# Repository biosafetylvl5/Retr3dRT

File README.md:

# Retr3dRT
RAMPS 1.4 self-test board designed for used in conjunction with Retr3d.

## Images

#### OSHPark Renderings

# Make Retr3dRT

## Parts

Check your parts! The easiest way to make an functional Retr3dRT and not know why it's not working to use the wrong parts.

Part            | Picture                                                                                                   | Description                                                | Quantity |                                                                              Distributer
--------------- | --------------------------------------------------------------------------------------------------------- | ---------------------------------------------------------- | :------: | ---------------------------------------------------------------------------------------:
Retr3dRT        |              | Circuit board, see "PCB Fabrication" for more info         |    1     |                                                                    OSH Park, SeeedStudio
4610X-101-502LF |  | Nine 5K Ohm Resistor Array, 10SIP                          |    2     |                                           [DigiKey](http://www.digikey.com/short/3p0zrv)
4610X-101-153LF |  | Five 15k Ohm Resistor Array, 10SIP                         |    4     |                                           [DigiKey](http://www.digikey.com/short/3p0zw4)
LED-3MM         |             | 3mm LED (Preferably Green)                                 |    1     |                                    [DigiKey](http://www.digikey.com/short/3p0z0f), Other
R1, R2          |         | 5k Ohm Resistor                                            |    2     |                                    [DigiKey](http://www.digikey.com/short/3p0z1c), Other
R3              |        | LED Current Limiting Resistor (520 Ohm is a safe estimate) |    1     |                                    [DigiKey](http://www.digikey.com/short/3p0z1r), Other
3461260P1       |       | DIP Long Blue Female Header                                |    7     | [Pending](http://www.seeedstudio.com/wiki/File:1X6P-2.54-8.5%2B2.5-12.3-BLUE-FEMALE.zip)

## Soldering

Now that you have your parts, let's get assembling! If you are just getting started in Electronics, check out [Lady Ada's Guide to Excellent Soldering](https://learn.adafruit.com/adafruit-guide-excellent-soldering/) to brush up on your soldering skills.

Start by soldering R1, R2, and R3 into place. Follow by soldering the LED paying special attention to the polarity annotated on the board. Next, solder the 4610X-101-153LFs and 4610X-101-502LFs by placing them in their holes and securing them with sticky tape. The stick tape prevents them from falling out as you turn the board upside down to solder.

Now, you should have all of the components except for the header soldered. To start the headers, get your diagonal cutters out. Use the diagonal cutters to cut the twelve long headers into eight four long headers, two five long header, one six long header, one eight long header and one complete twelve long header. Now that all of your headers have been prepared, plug them into your RAMPS control board that has its **stepper drivers installed**. Now, carefully lower your Retr3dRT onto the pins and solder it in place.

## Using

Download [Retr3dRT.ino](https://raw.githubusercontent.com/biosafetylvl5/Retr3dRT/master/Retr3dRT.ino) from the [Retr3dRT repository](https://github.com/biosafetylvl5/Retr3dRT) and upload it to your Arduino MEGA with both RAMPS and Retr3dRT installed on top. To view the diagnosis, open your serial terminal and bask in the glow of the information.

## Keeping in touch

To keep in touch to watch for updates and improvements you have a few options:

- [Star the Retr3dRT repository](https://github.com/biosafetylvl5/Retr3dRT/stargazers) to be kept up to date
- Follow the [#Retr3dRT hashtag](https://twitter.com/hashtag/Retr3dRT?f=tweets&src=hash) on twitter to know the moment things happen
- Check out [techfortrade](techfortrade.org) to see what else we're doing

## PCB Fabrication
We're lucky enough to live in the era of cheap and abundant PCB fabrication options. However, this abundance of choices does make choosing a formidable task. However, too make the choosing easier for you, we've narrowed down
the choices to two for you. You're free to choose any fabrication vendor, but we will only be offering (unless asked for others) gerber files (PCB blueprints) for SeeedStudio and OSHPark.

### OSHPark
OSHPark is fantastic. Their boards look great and arrive quickly. However, at 5$ per square inch for three boards, they can be costly for larger runs. Other than that, they have produced good results. This is probably the choice for you if you need
three boards or less.

### SeeedStudio
While SeeedStudio is the budget choice, this isn't a statement about their quality. They feature vanilla PCBs that are very functional, but aren't the most aesthetically pleasing. They deliver quickly, but slower than OSHPark (in the USA) given that they're based in china. This is probably the choice for you if you need more than three boards.

### Final Notes

This board assumes that PCB traces are not faulty. Although this is a possibility, the board was not designed explicitly to test poor traces, it is highly probable that the results from tests meant to test intra-board connections will also flag trace problems.

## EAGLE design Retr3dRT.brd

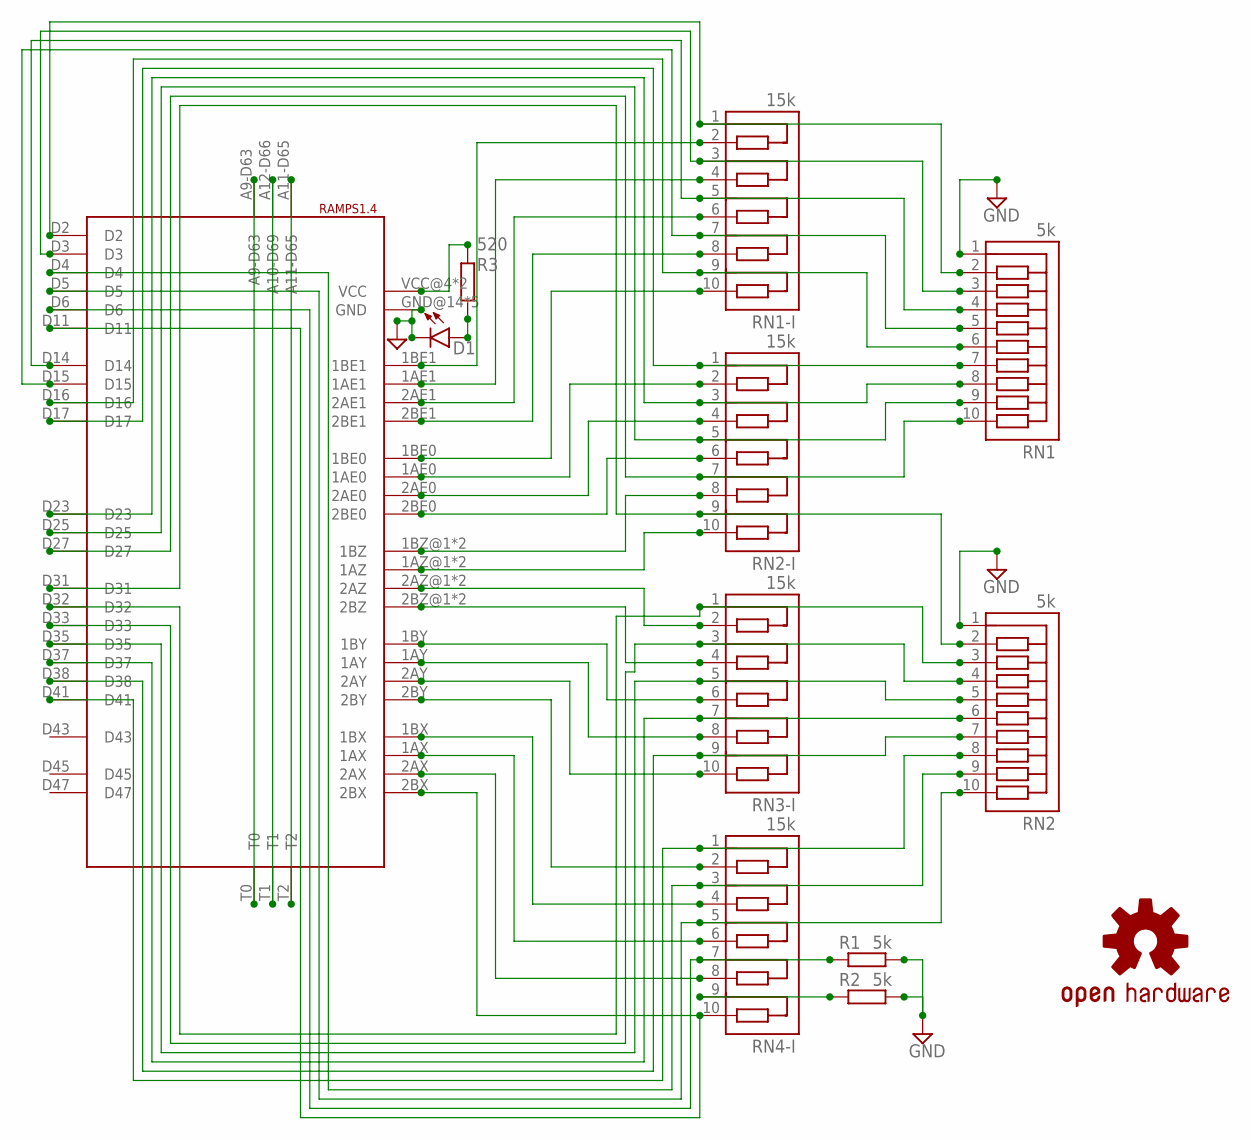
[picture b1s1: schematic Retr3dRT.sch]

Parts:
D1: LED; LED3MM-NS
LOGO2: OSHW-LOGOL-COPPER; OSHW-LOGO-L_COPPER
R1, R2: 5k; 0204/7
R3: 520; 0204/7
RAMPS1.4: RAMPS2
RN1, RN2: 5k; RN10
RN1-I, RN2-I, RN3-I, RN4-I: 15k; RN10

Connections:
GND: D1.K (C), R1.2, R2.2, RAMPS1.4.GND@14 (GND), RAMPS1.4.GND@16 (GND), RAMPS1.4.GND@17 (GND), RAMPS1.4.GND@18 (GND), RAMPS1.4.GND@19 (GND), RN1.1, RN2.1
unnamed: RAMPS1.4.D23, RN1.8, RN2-I.3
unnamed: RAMPS1.4.2AZ@1 (2AZ), RAMPS1.4.2AZ@2 (2AZ), RN3-I.2
unnamed: RAMPS1.4.1BY, RN3-I.6
unnamed: RAMPS1.4.2AY, RN3-I.10
unnamed: RAMPS1.4.2BY, RN4-I.2
unnamed: RAMPS1.4.1BX, RN4-I.4
unnamed: RAMPS1.4.1AX, RN4-I.6
unnamed: RAMPS1.4.1AY, RN3-I.8
unnamed: R1.1, RAMPS1.4.D6, RN4-I.7
unnamed: RAMPS1.4.2BZ@1 (2BZ), RAMPS1.4.2BZ@2 (2BZ), RN3-I.4
unnamed: D1.A, R3.2
unnamed: RAMPS1.4.2BX, RAMPS1.4.D11, RN4-I.10
unnamed: R2.1, RN4-I.9
unnamed: RAMPS1.4.A11-D65, RAMPS1.4.T2
unnamed: RAMPS1.4.A12-D66 (A10-D69), RAMPS1.4.T1
unnamed: RAMPS1.4.A9-D63, RAMPS1.4.T0
unnamed: RAMPS1.4.D17, RN1.7, RN2-I.1
unnamed: RAMPS1.4.D16, RN1.6, RN1-I.9
unnamed: RAMPS1.4.D25, RN1.9, RN2-I.5
unnamed: RAMPS1.4.D31, RN2.2, RN2-I.9
unnamed: RAMPS1.4.1BE1, RN1-I.2
unnamed: RAMPS1.4.1AE1, RN1-I.4
unnamed: RAMPS1.4.2AE1, RN1-I.6
unnamed: RAMPS1.4.2BE1, RN1-I.8
unnamed: RAMPS1.4.1BE0, RN1-I.10
unnamed: RAMPS1.4.1AE0, RN2-I.2
unnamed: RAMPS1.4.2AE0, RN2-I.4
unnamed: RAMPS1.4.2BE0, RN2-I.6
unnamed: RAMPS1.4.1BZ@1 (1BZ), RAMPS1.4.1BZ@2 (1BZ), RN2-I.8
unnamed: RAMPS1.4.1AZ@1 (1AZ), RAMPS1.4.1AZ@2 (1AZ), RN2-I.10
unnamed: RAMPS1.4.2AX, RN4-I.8
unnamed: RAMPS1.4.D2, RN1.2, RN1-I.1
unnamed: RAMPS1.4.D3, RN1.3, RN1-I.3
unnamed: RAMPS1.4.D14, RN1.4, RN1-I.5
unnamed: RAMPS1.4.D15, RN1.5, RN1-I.7
unnamed: RAMPS1.4.D27, RN1.10, RN2-I.7
unnamed: RAMPS1.4.D32, RN2.3, RN3-I.1
unnamed: RAMPS1.4.D33, RN2.4, RN3-I.3
unnamed: RAMPS1.4.D35, RN2.5, RN3-I.5
unnamed: RAMPS1.4.D37, RN2.6, RN3-I.7
unnamed: RAMPS1.4.D38, RN2.7, RN3-I.9
unnamed: RAMPS1.4.D41, RN2.8, RN4-I.1
unnamed: RAMPS1.4.D4, RN2.9, RN4-I.3
unnamed: RAMPS1.4.D5, RN2.10, RN4-I.5
VCC: R3.1, RAMPS1.4.VCC@4 (VCC), RAMPS1.4.VCC@6 (VCC)

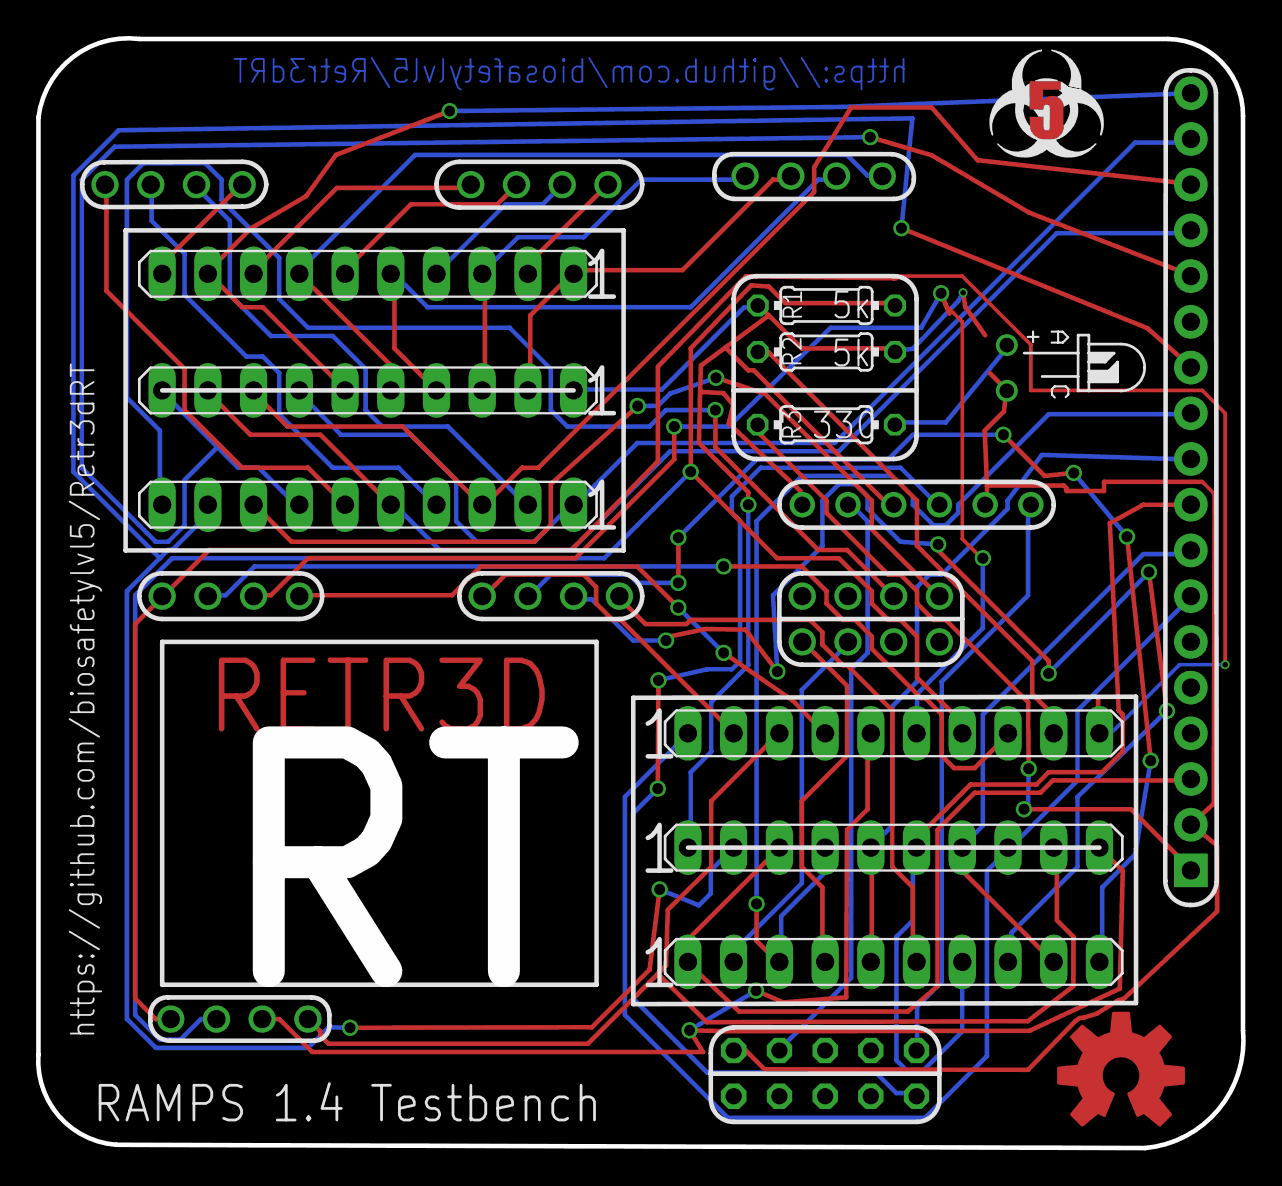
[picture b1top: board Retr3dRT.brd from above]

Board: 4 copper layers, 67.0 x 61.7 mm, 14 parts (0 on the bottom side), 46 nets.

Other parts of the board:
E$1: BSL-5-SLK-SML
U$2: LED-GUIDE

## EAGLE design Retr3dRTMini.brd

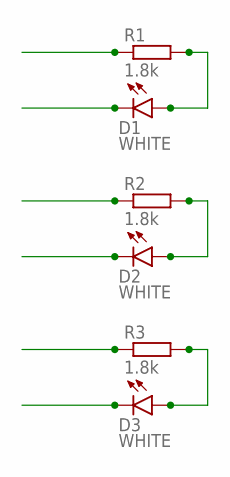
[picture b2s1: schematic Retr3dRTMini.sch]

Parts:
D1, D2, D3: WHITE; LED-1206
R1, R2, R3: 1.8k; R0805

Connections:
unnamed: D1.A, R1.2
unnamed: D2.A, R2.2
unnamed: D3.A, R3.2
S1: D1.C
S2: R1.1
S3: D2.C
S4: R2.1
S5: D3.C
S6: R3.1

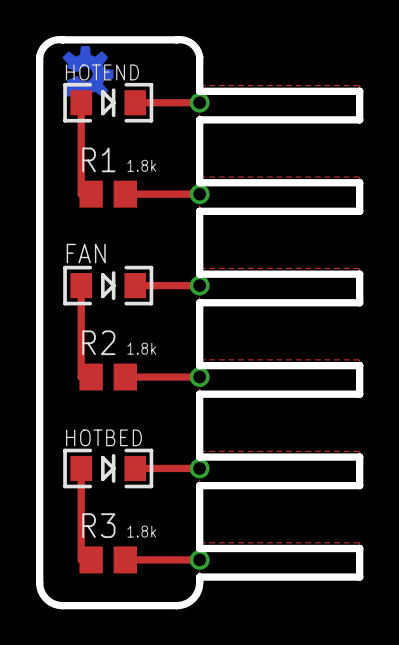
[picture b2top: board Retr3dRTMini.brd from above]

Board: 2 copper layers, 17.8 x 31.4 mm, 7 parts (0 on the bottom side), 3 nets.

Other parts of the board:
U$1: OSHW-LOGO-S_COPPER

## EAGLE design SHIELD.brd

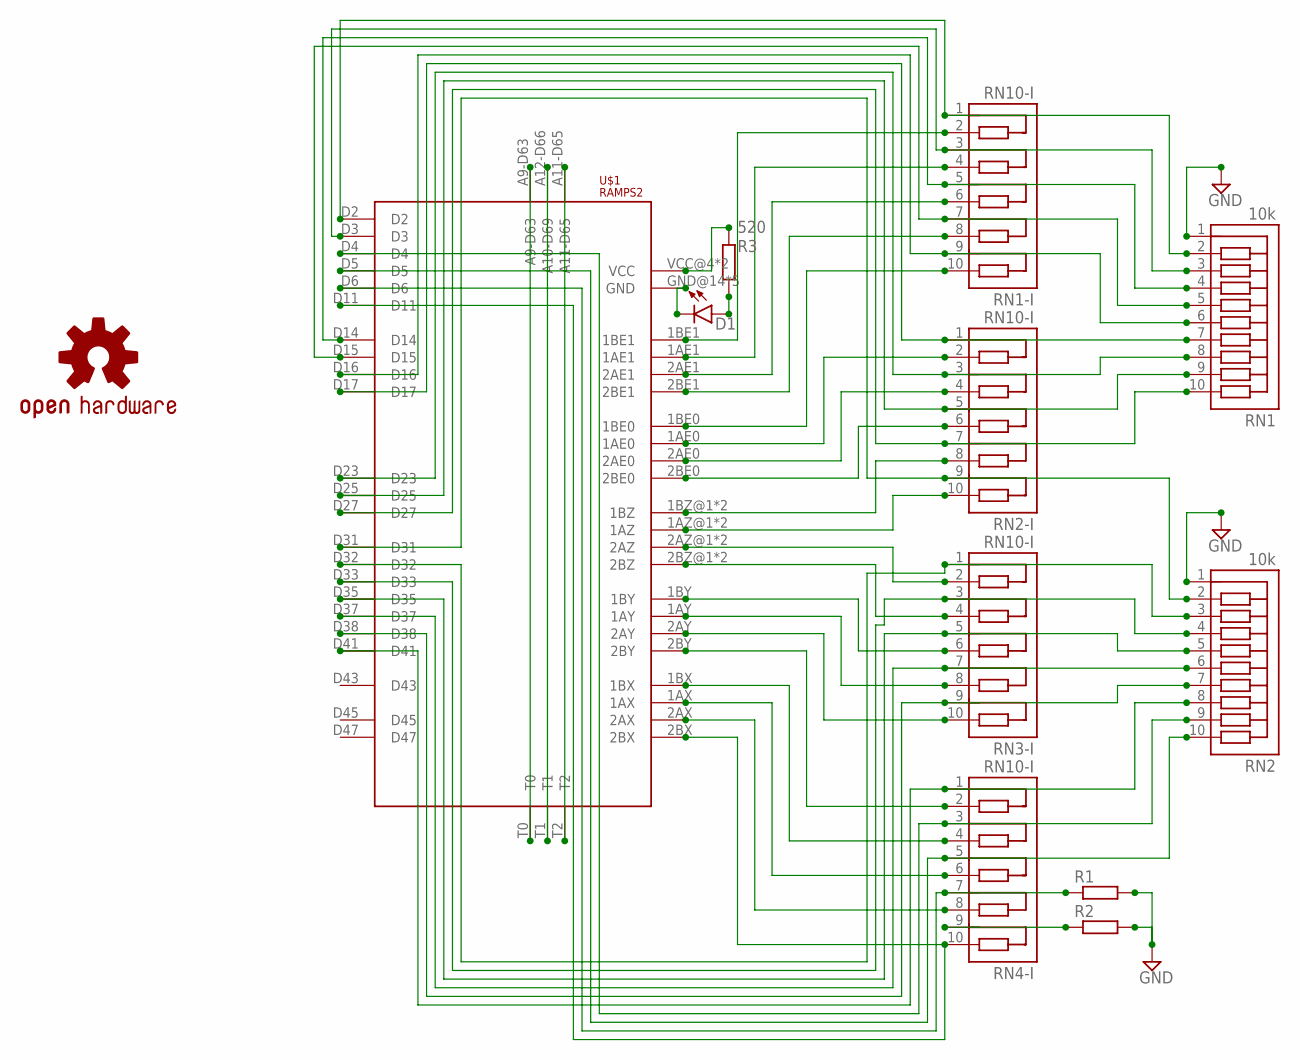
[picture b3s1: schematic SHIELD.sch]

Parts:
D1: LED-3MM-NO_SILK; LED3MM-NS
LOGO2: OSHW-LOGOL-COPPER; OSHW-LOGO-L_COPPER
R1, R2: R-EU_0204/7; 0204/7
R3: 520; 0204/7
RN1, RN2: 10k; RN10
RN1-I, RN2-I, RN3-I, RN4-I: RN10-I; RN10
U$1: RAMPS2

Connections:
GND: R1.2, R2.2, RN1.1, RN2.1
unnamed: RN1.8, RN2-I.3, U$1.D23
unnamed: RN3-I.2, U$1.2AZ@1 (2AZ), U$1.2AZ@2 (2AZ)
unnamed: RN3-I.6, U$1.1BY
unnamed: RN3-I.10, U$1.2AY
unnamed: RN4-I.2, U$1.2BY
unnamed: RN4-I.4, U$1.1BX
unnamed: RN4-I.6, U$1.1AX
unnamed: RN3-I.8, U$1.1AY
unnamed: D1.K (C), U$1.GND@14 (GND), U$1.GND@16 (GND), U$1.GND@17 (GND), U$1.GND@18 (GND), U$1.GND@19 (GND)
unnamed: R3.1, U$1.VCC@4 (VCC), U$1.VCC@6 (VCC)
unnamed: R1.1, RN4-I.7, U$1.D6
unnamed: RN3-I.4, U$1.2BZ@1 (2BZ), U$1.2BZ@2 (2BZ)
unnamed: D1.A, R3.2
unnamed: RN4-I.10, U$1.2BX, U$1.D11
unnamed: R2.1, RN4-I.9
unnamed: U$1.A11-D65, U$1.T2
unnamed: U$1.A12-D66 (A10-D69), U$1.T1
unnamed: U$1.A9-D63, U$1.T0
unnamed: RN1.7, RN2-I.1, U$1.D17
unnamed: RN1.6, RN1-I.9, U$1.D16
unnamed: RN1.9, RN2-I.5, U$1.D25
unnamed: RN2.2, RN2-I.9, U$1.D31
unnamed: RN1-I.2, U$1.1BE1
unnamed: RN1-I.4, U$1.1AE1
unnamed: RN1-I.6, U$1.2AE1
unnamed: RN1-I.8, U$1.2BE1
unnamed: RN1-I.10, U$1.1BE0
unnamed: RN2-I.2, U$1.1AE0
unnamed: RN2-I.4, U$1.2AE0
unnamed: RN2-I.6, U$1.2BE0
unnamed: RN2-I.8, U$1.1BZ@1 (1BZ), U$1.1BZ@2 (1BZ)
unnamed: RN2-I.10, U$1.1AZ@1 (1AZ), U$1.1AZ@2 (1AZ)
unnamed: RN4-I.8, U$1.2AX
unnamed: RN1.2, RN1-I.1, U$1.D2
unnamed: RN1.3, RN1-I.3, U$1.D3
unnamed: RN1.4, RN1-I.5, U$1.D14
unnamed: RN1.5, RN1-I.7, U$1.D15
unnamed: RN1.10, RN2-I.7, U$1.D27
unnamed: RN2.3, RN3-I.1, U$1.D32
unnamed: RN2.4, RN3-I.3, U$1.D33
unnamed: RN2.5, RN3-I.5, U$1.D35
unnamed: RN2.6, RN3-I.7, U$1.D37
unnamed: RN2.7, RN3-I.9, U$1.D38
unnamed: RN2.8, RN4-I.1, U$1.D41
unnamed: RN2.9, RN4-I.3, U$1.D4
unnamed: RN2.10, RN4-I.5, U$1.D5

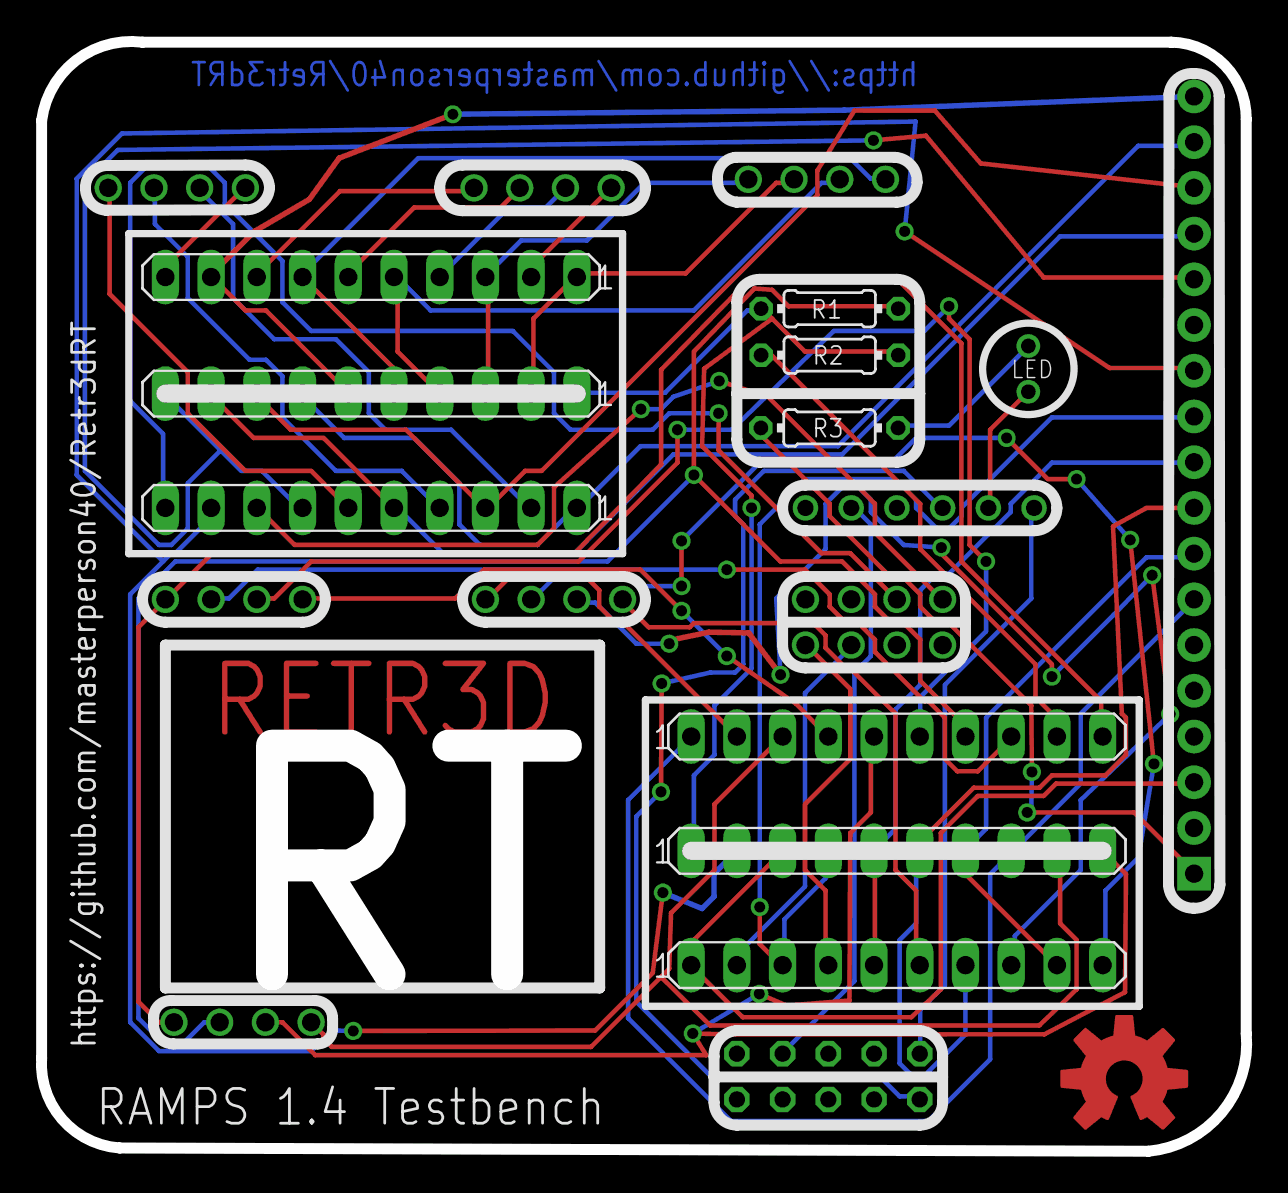
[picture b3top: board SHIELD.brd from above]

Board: 2 copper layers, 67.0 x 61.7 mm, 12 parts (0 on the bottom side), 47 nets.

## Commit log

2016-03-08 Inital Commit
2016-03-15 Added images
2016-03-15 Updated Design
2016-03-26 Schematic Changes
2016-03-26 Added Retr3dRTMini
2016-03-26 Higher Resolution Images
2016-03-26 Added pictures of Retr3dRTMini OSH Park Renderings
2016-03-26 Aesthetic Changes
2016-03-31 Added Gerbers
2016-05-30 Fixed disconnect between grounds
2016-05-30 Added OSHPark Gerbers
2016-05-30 Added Arduino Sketch
2016-05-30 Fixed silkscreen of R1 and R2
2016-05-30 Added Seeed Gerbers
2016-05-30 Updated Board Images
2016-05-30 Added Component Images
2016-05-30 Made Images Transparent
2016-05-30 Added header image
2016-05-30 Added header image (fixed)
2016-05-30 Updated images
2016-05-30 Fixed images in README
2016-05-31 Added PCB Fab Section

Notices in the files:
parts and their libraries:
SparkFun-LED: Licensing: Creative Commons ShareAlike 4.0 International - https://creativecommons.org/licenses/by-sa/4.0
